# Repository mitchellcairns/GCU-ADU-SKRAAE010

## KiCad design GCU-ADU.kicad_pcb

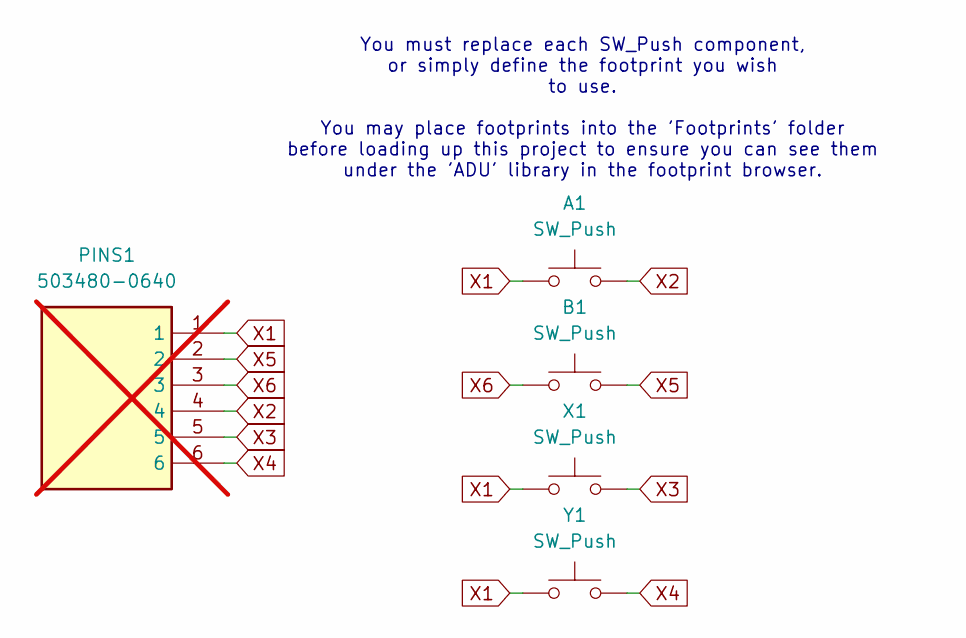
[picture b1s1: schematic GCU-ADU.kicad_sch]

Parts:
A1: SW_Push; SKRR
B1: SW_Push; SKRR
PINS1: 503480-0640; molex_5034800640_ribbon; Mouser Part Number 538-503480-0640; not fitted
X1: SW_Push; SKRR
Y1: SW_Push; SKRR

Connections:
X1: A1.1, PINS1.1, X1.1, Y1.1
X2: A1.2, PINS1.4
X3: PINS1.5, X1.2
X4: PINS1.6, Y1.2
X5: B1.2, PINS1.2
X6: B1.1, PINS1.3

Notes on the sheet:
You must replace each SW_Push component, or simply define the footprint you wish to use. You may place footprints into the 'Footprints' folder before loading up this project to ensure you can see them under the 'ADU' library in the footprint browser.

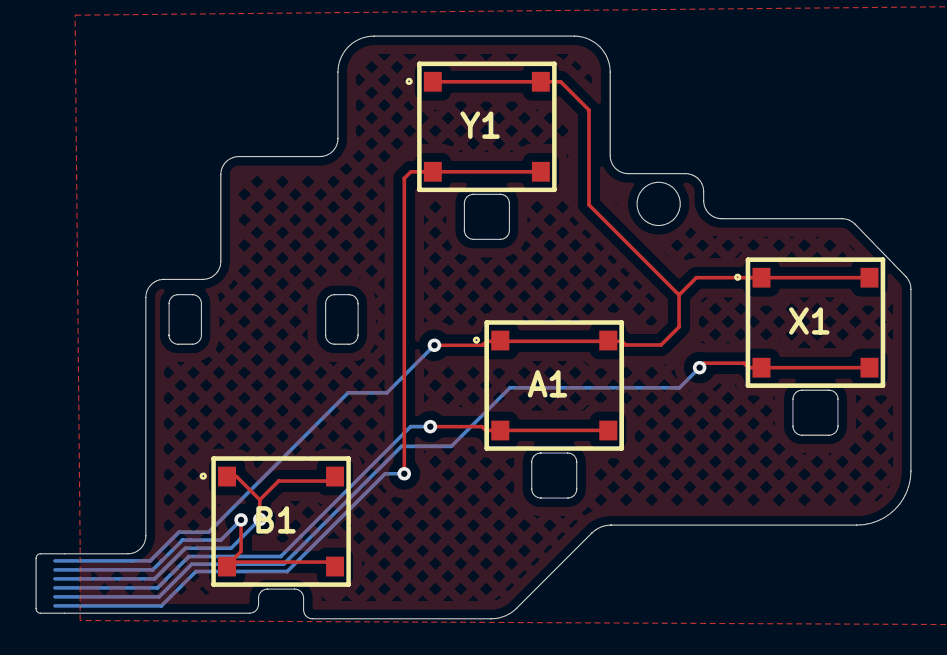
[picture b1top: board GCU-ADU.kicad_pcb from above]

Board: 2 copper layers, 48.6 x 32.4 mm, 5 parts (1 on the bottom side), 6 nets.

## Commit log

2025-03-01 Add switches to schematic
